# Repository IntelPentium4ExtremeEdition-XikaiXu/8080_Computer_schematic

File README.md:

# 8080_Computer_schematic
Contribution_of_kiCad_Study

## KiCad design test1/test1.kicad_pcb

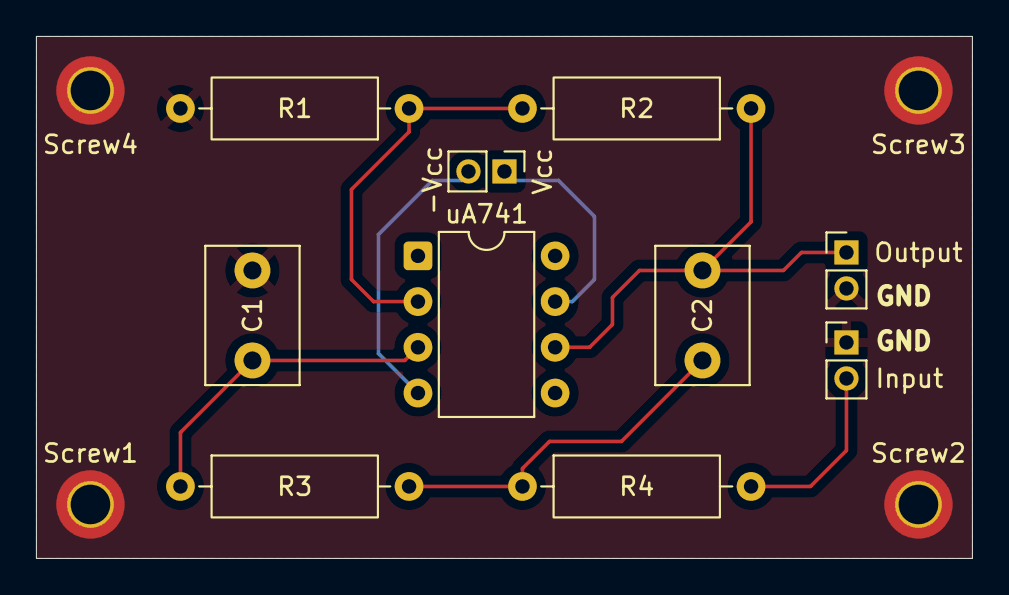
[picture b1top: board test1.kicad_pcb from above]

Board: 2 copper layers, 52.0 x 29.0 mm, 14 parts (0 on the bottom side), 8 nets.

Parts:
C1, C2: 0.00000001; C_Disc_D7.5mm_W5.0mm_P5.00mm
Input: Conn_01x02_Pin; PinHeader_1x02_P2.00mm_Vertical
Output: Conn_01x02_Pin; PinHeader_1x02_P2.00mm_Vertical
R1, R2, R3, R4: 2000; R_Axial_DIN0309_L9.0mm_D3.2mm_P12.70mm_Horizontal
Screw1, Screw2, Screw3, Screw4: MountingHole_Pad; MountingHole_2.2mm_M2_DIN965_Pad_TopBottom
Vcc: Conn_01x02_Pin; PinHeader_1x02_P2.00mm_Vertical
uA741: LT6238; DIP-8_W7.62mm

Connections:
+5V: Vcc.1, uA741.7 (VCC)
-5V: Vcc.2, uA741.4 (VEE)
GND: C1.2, Input.1 (GND), Output.2 (Input), R1.2, Screw1.1, Screw2.1, Screw3.1, Screw4.1
Input: Input.2 (Input), R4.2
unnamed: C2.1, R3.2, R4.1
unnamed: C1.1, R3.1, uA741.3 (IN+)
unnamed: R1.1, R2.2, uA741.2 (IN-)
Output: C2.2, Output.1 (GND), R2.1, uA741.6 (OUT)

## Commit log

2025-10-11 test 1
2025-10-11 new update
2025-10-11 test
2025-10-11 init
